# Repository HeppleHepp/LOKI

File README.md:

# README

## LOKI

Developement of telemetry and data collection using a microcontroller \(Arduino, ESP32 etc\) to output a PWM signal to a speed controller such as the 4QD porter 5/10.

In this repository you will find incremental developement to find the best solution to operating and using 24V DC batteries and motor as found on the Greenpower \(www.greenpower.co.uk\) regulations page. Electronics \(Loki Board\) and the software is free of licence, however, the board will be made available to purchase directly from me as a private agreement. \(email: coalescence.gp@gmail.com\), but feel free to try and have a good hack at it ;\).

## History:

Back in 2019 I had started my A-level in Design Technology and wanted to create a product that would allow better team communication, this eventually transpired to making a battery status monitor that beamed an 433MHz signal to the pitlane during the races. The voltage was found using a potential divider on a raspberry Pi and the string was encoded into a Hex signal which then used precise timers to create the packets needed to allow AM carrier transmition.

This was a massive headache, clunky and inefficient \(But I got the A\* i needed hehe\).

In March 2020, during the covid-19 pandemic, I suddenly found that I had plenty of time to think of a better solution, which was when I started to research about hobbiest electronics and microcontrollers such as the arduino. They offered a more efficient/code logic rather than using logic gates to encode data. Also, having a microcontroller allowed for more data to be gathered, which was the moment I realised much, much more could be achieved. Since then I have been developing sensor data based circuits that can monitor a greenpower cars 'vital systems'. In July 2020 I was no longer a member of BGS Greenpower \(Bristol Grammar School\) and I joined a close friend's team called Coalescence GP which included his first car Icarus. With a new team and direction I set about making the next car monitoring system.

The first version of this was called T2W \(The Thrust Weapon, don't ask why\) and while it was rigged with glitches and poor design ethos it did the job and in september of 2020 gave us some valuable current vs time data, saved to an SD card, which is arguably the most important data you can collect. There was capability to gather voltage, Temperature, and RPM, but a lack of a solid testing environment due to COVID meant it was the first time the board was being used in that environment. But still I was determined to get a better understanding of the potential microcontrollers offered.

Loki is my latest developent of this journey, and is the design I hope to iterate on over at least the next 2 years. I will be developing it in parallel with my course at university and will deploy updates and provide active support to anyone who wishes to use the board.

## Board features:

Firstly, it cannot be ignored that anyone who has previously looked at different option for adding data telemetry and monitoring of systems has more than likely come across the WeChook racing fellas who developed a very realiable system called the Echook Nano which is arguably the most widely used kit that fulfills this purpose. It offers pretty much the exact same features as LOKI, but having been in development for many years now it does offer a more tried and relaible system. The Echook Nano documentaion \([https://docs.echook.uk/](https://docs.echook.uk/)\), has offered me with plenty of wisdom and I have also spoken to the very active developers to confer with them over design choices for LOKI, so they only have my graditude and I have no intention of competing with them \(don't think I could even if I tried to be honest\). However, didn't stop me from trying to make my own custom board that fulfills my own specification and allows me to tailor it to my needs. All in all, thanks Rowan :D

**Features included:**

**Current sensing** up to 150 amps with a resolution of 0.25A \(Could be improved with an Op Amp :/ \)

**Battery voltage** reading \(Max 30V as there is a 1/6 ratio to step down to the 5V arduino Pin \)

**Motor RPM** \(This is done using an infrared variable distance circuit that triggers an external interrupt on the board\)

**Motor Temperature** \(This only samples the temperature with a very high accuracy every 6 seconds because does take considerable processing power\)

**Race Time** \(Only records the time since the board was switched on. So if the +24V into the board is turned off when the car is turened of the clock will reset\)

**Data Logging** \( saves all the above data into a text document, with each variable seperated by a comma which excel loves :\) \)

**Bluetooth Extension** \(A bit of a last ditch addition, there is no functionality in the software to use this currently, but it's there incase you wish to develope that yourself\)

**2 Button inputs** \(Named on the board as Throttle and Boost, This can be configured as other functions if you are using a Variable throttle\)

**2 Variable throttle or ADC ports** \(These are left spare so addition sensors or a twist grip throttle can be added onto the board where required \(some exceptions will apply\)\).

**For more information please open the PDF in the Main commit**

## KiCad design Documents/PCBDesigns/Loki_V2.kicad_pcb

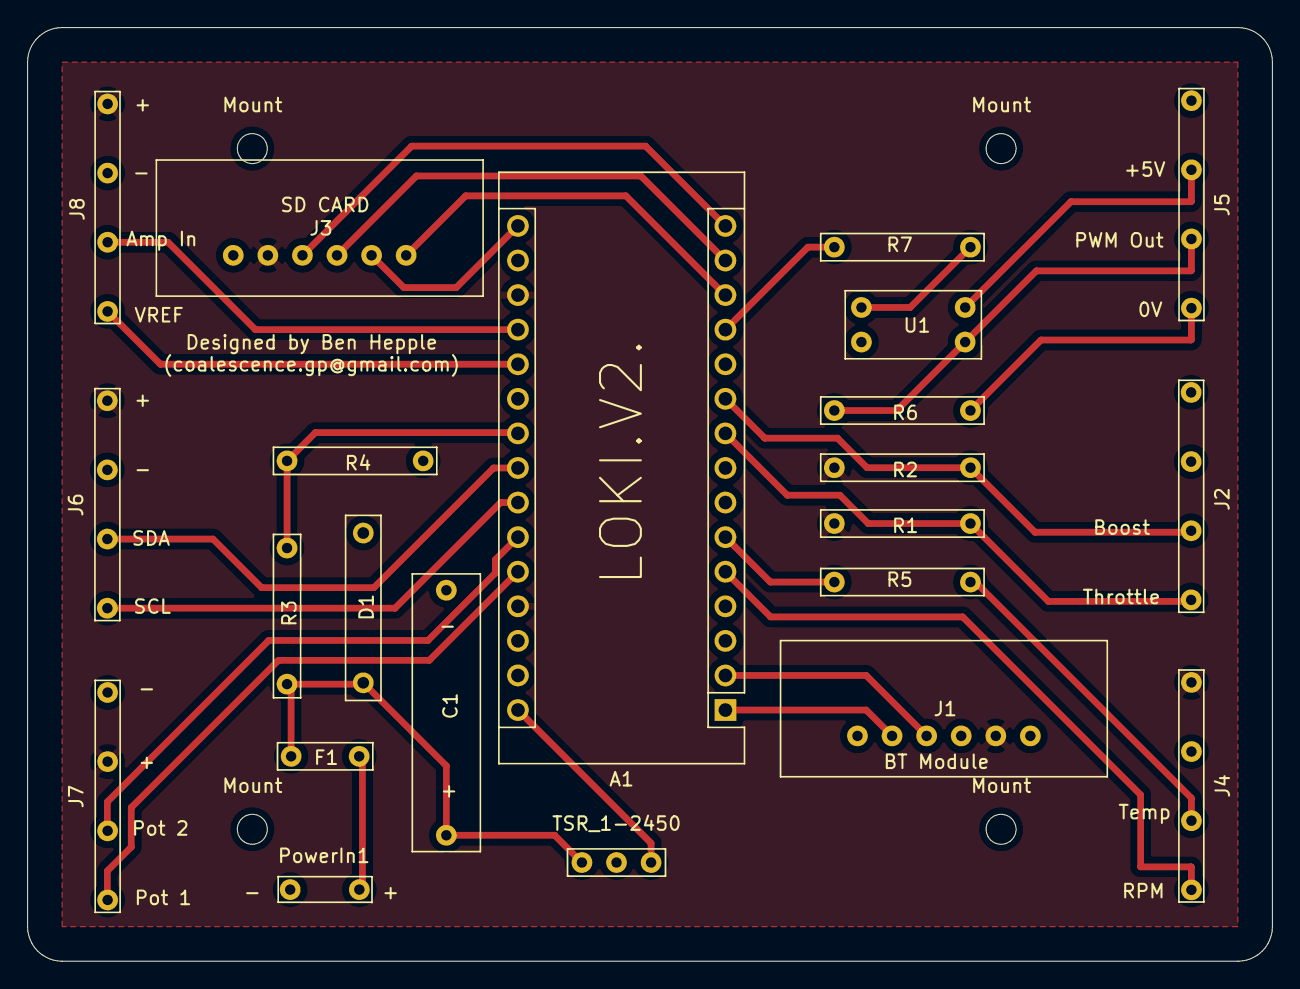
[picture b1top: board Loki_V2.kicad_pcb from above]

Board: 2 copper layers, 91.4 x 68.6 mm, 26 parts (0 on the bottom side), 28 nets.

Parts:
A1: Arduino_Nano_v3.x; Arduino_Nano
C1: 22uF 63V; 22uF_Axial_Capacitor
D1: 1N5819RLG; Schottky
F1: 0.5A P-Fuse; PolyFuse
J1: Bluetooth_Ext; SD_Card
J2: Bool_Input; Screw_Terminal_X4
J3: SD Card Port; SD_Card
J4: RPM&Temp; Screw_Terminal_X4
J5: PWM Out; Screw_Terminal_X4
J6: LCD Display; Screw_Terminal_X4
J7: Dual Pot; Screw_Terminal_X4
J8: Current Sensor; Screw_Terminal_X4
Mount: MountingHole_2.2mm_M2
Mount#2, Mount#3, Mount#4: MountingHole_2.2mm_M2
PowerIn1: Input; Screw_Terminal_X2
R1, R2: 10K; Default_Resistor
R3: 82K; Default_Resistor
R4: 16K; Default_Resistor
R5: 5.1K; Default_Resistor
R6, R7: R; Default_Resistor
TSR_1-2450: Screw_Terminal_01x03; 2.54mmX3
U1: SFH617A-1; Optocoupler_K1010_B

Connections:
0V: A1.4, C1.2, D1.2, J1.4, J2.1, J2.2, J3.1, J4.3, J6.1, J7.2, J8.3, PowerIn1.2, R4.2, TSR_1-2450.2, U1.2
+5V: A1.18, A1.27, J1.5, J3.2, J4.4, J6.2, J7.1, J8.4, R1.1, R2.1
+24V: C1.1, D1.1, F1.1, R3.1, TSR_1-2450.3
Amp_In: A1.19, J8.1
BT_Input: A1.2, J1.3
BT_Output: A1.1, J1.2
Bat_Read: A1.22, R3.2, R4.1
Boost: A1.10, J2.3, R2.2
ChipSelect: A1.13, J3.6
MISO: A1.15, J3.3
MOSI: A1.14, J3.4
unnamed: F1.2, PowerIn1.1
unnamed: J4.1, R5.1
unnamed: J5.1, U1.4
unnamed: J5.3, R6.1, U1.3
unnamed: J5.4, R6.2
unnamed: R7.1, U1.1
PWM: A1.12, R7.2
Pot_1: A1.25, J7.3
Pot_2: A1.26, J7.4
RPM_Int: A1.5, J4.2
SCK: A1.16, J3.5
SCL: A1.24, J6.4
SDA: A1.23, J6.3
Temp: A1.6, R5.2
Throttle: A1.9, J2.4, R1.2
VREF: A1.20, J8.2
Vin: A1.30, TSR_1-2450.1

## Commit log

2021-02-23 Create Photos
2021-02-23 Create Changelog
2021-02-23 Create yes
2021-02-23 KiCad file upload
2021-02-23 Add PCB file
2021-02-23 added photos to combe2020
2021-02-25 GitBook: [master] 5 pages and 6 assets modified
2021-02-25 GitBook: [main] 5 pages and 8 assets modified
2021-02-25 GitBook: [master] 4 pages and 2 assets modified
2021-02-25 GitBook: [main] 3 pages modified
2021-02-25 GitBook: [master] 7 pages and 2 assets modified
